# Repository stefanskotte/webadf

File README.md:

# WebFloppy

An Amiga disk library that puts a disk in a real Amiga's floppy drive over WiFi. (The repository keeps the
project's first name, `webadf`.)

Two halves that work together:

- **A web app** for keeping Amiga disk images. Add them, have them identified
  against TOSEC, OpenRetro and Demozoo, organise them into collections, browse and
  edit the files inside a disk, rewind a disk to any earlier version, and send files to
  and from the Amiga.
- **A drive replacement.** An RP2350 board plugs into the Amiga's floppy connector,
  behaves like a DD or HD floppy drive, and plays whichever disk you pick in the web app.
  When the Amiga saves, the changes go back to the library.

Run the web app two ways: use our hosted copy at <https://webadf.vercel.app> (on Vercel), or
host your own with Docker on any amd64 or arm64 machine, a NAS included. A self-hosted copy has every
feature the hosted one has. Firmware updates, the PaulaNET driver disk and the TOSEC catalogue
arrive by themselves; see [docs/self-hosting.md](docs/self-hosting.md).

Pick a disk in the browser, or tap its NFC tag on the drive, and the Amiga reads it.
Workbench 3.1 boots from the board, games load, and saves made on the Amiga show up
in the web app as new versions of the disk.

*Rev B, designed by Shanshe: 34-pin floppy header, floppy power connector, OLED
display, buzzer, a 4-pin header (J4), and a Pimoroni Pico Plus 2 W.
The KiCad project is in `wifi-floppy/hardware/`; check it with `pnpm hw:verify` before
ordering. Rev B has been the bench board since October 2026.*

## Bugs and ideas

Found a bug, or want something WebFloppy does not do yet? Anyone can open an issue at
<https://github.com/stefanskotte/webadf/issues>, for a bug report or a feature request alike. For a bug, say what
you did, what you saw and, for a board, which firmware it runs (Devices shows it).

## Quickstart

Choose where the web app runs. The board's first install is the same either way; only a
self-hosted copy needs one extra step, pointing the board at your server.

### Path A: the hosted web app (Vercel)

You need the board, a USB cable, a phone and an account on <https://webadf.vercel.app>
(registration is by invitation). The board talks to this server out of the box.

1. Hold the **BOOT** button (the Raspberry Pi docs call it BOOTSEL) and plug the board into
   your computer over USB. A drive called `RP2350` appears.
2. Download `wifi-floppy-install-<version>.uf2` from the
   [latest release](https://github.com/stefanskotte/webadf/releases/latest) and drag it onto
   that drive. The board writes it and restarts by itself; the drive disappears.
3. **Get a pairing code in the web app.** The code comes from the web app, not the board. Open
   **Devices**: with no board yet it lists the five steps (**How pairing works** shows them again at any
   time). Press **Pair a device**, give the board a name and press **Get a code**. The code lasts 30 minutes,
   and the page now walks you through the rest with the code filled in.

4. **Give the board your Wi-Fi and the code.** Power the board; its screen shows *Setup needed* and its own
   Wi-Fi network, `wifi-floppy-XXXX`. Join that network from your phone (password `wififloppy`). The
   setup page opens by itself; if it does not, browse to `http://192.168.4.1/`. Enter your home Wi-Fi name
   and password (a 2.4 GHz network with a password) and the code, and press **Save**.

5. **Wait about a minute.** The board's network disappears, the board joins your Wi-Fi and uses the code
   to register with the web app. Keep the Devices page open: it says **Paired** and shows the board by
   itself. If the board cannot join or register, its setup network comes back with the reason at the top
   of the setup page; join it again and fix that. Firmware updates now arrive over the air from the web app.

### Path B: your own server (self-hosted, Docker)

You need a host with Docker and Compose v2, the board, a USB cable and a phone.

1. Install the stack, as [docs/self-hosting.md](docs/self-hosting.md#2-install) describes: download
   `compose.yaml` and `.env.example` (as `.env`) from the newest `web-X.Y.Z` tag, set `WEBADF_URL`
   (for example `https://192.168.1.10`) and `WEBADF_ADMIN_EMAIL` in `.env`, then run
   `docker compose up -d`. Create the account with the link from `docker compose logs app | grep 'first admin'`.
2. Install the firmware as in steps 1-2 of Path A.
3. **Override the server.** The firmware points at the hosted app by default. Open the board's
   USB serial console (any serial terminal, firmware 1.13.0 or newer) and type:

   ```
   wf server set https://192.168.1.10
   wf server tls noverify
   YES
   wf reboot
   ```

   Use your own `WEBADF_URL`. `tls noverify` is needed because a board cannot trust the
   certificate Caddy makes for an IP address or a LAN name; with a public `WEBADF_DOMAIN` and a
   Let's Encrypt certificate, leave it out. `wf server show` prints the setting and
   `wf server clear` goes back to the hosted app. Changing the server forgets the board's
   Wi-Fi and pairing, and it refuses while a disk is mounted.
4. Pair it as in steps 3-5 of Path A, from **Devices** on your own server. Firmware updates come
   from your server too: it imports every signed release from GitHub daily.

If your phone has joined this board's setup network before, forget that network first. More
detail, and what to do when a join fails, is in
[wifi-floppy/README.md](wifi-floppy/README.md#first-install) and, for a self-hosted copy,
[docs/self-hosting.md](docs/self-hosting.md#4-boards).

## Screenshots

The pictures come from a demo account holding freely redistributable disks: scene demos and
freeware tools. `PORT=3100 pnpm screenshots` takes them again (see
`e2e/screenshots.shots.ts`); every email address on them is masked, and the board is a
stand-in called A500. The one exception is Transfer's window, captured from a real A500 by hand.

*The library. Titles are identified against TOSEC and Demozoo; the 9 Fingers card is
outlined and carries a DF0 pill because its disk is in a drive.*

*The drive menu in the header: from any page, see what each board is playing, switch write
protection, step to the next disk or eject.*

*A title page: facts and screenshots from Demozoo, then each disk with its actions.*

*Files: two panes in the Directory Opus style over STASH:, NET: and LIBRARY: (collections are folders there). The pane
you last clicked is the source; the buttons under the panes act on it. Each edit to a disk is a new version in its History.*

*NET: also lists the Amiga's own volumes when Transfer runs there with Read ticked: open a drawer on the hard disk
and copy files to STASH: or LIBRARY:. With Write ticked too, copy and move onto it, rename and delete.*

*Transfer, on the Amiga itself: files from the web app arrive here, and Send goes the other way. Read and Write decide
what the web app may do with the Amiga's volumes.*

*A board on the Devices page. The drawing's screen shows what the board's OLED shows.*

*The display editor: choose the panel, then which elements the OLED draws and where.*

*Adding disks: drop them anywhere on the Library page, or use Add disks (Browse files, Paste a URL). The tray says
what each one did.*

*Help explains the parts that are not obvious.*

*Settings has three tabs: Account (yours alone), Library (sharing) and Server.*

*Sharing, on the Library tab: let a friend's WebFloppy browse and mount your collections. Each link works once.*

*About this server, on the Server tab.*

*On a phone or a tablet (below 1024 px wide), the pages move to a tab bar at the bottom; More holds the rest.*

*The server admin's Overview, for whoever runs the copy.*

## Features

### Library

- Add `.adf`, `.adz`, `.dms`, `.dmz` and `.hfe` by dropping them anywhere on the Library page (folders and
  `.zip` / `.lha` of them too) or through Add disks: Browse files, or Paste a URL to one (or to a `.zip` or `.lha`
  of them, up to 20 MB). Drop `.lha`, `.lzh` and `.zip` archives onto a disk to pick files out of them.
- HD (1.76 MB) ADFs are recognised and tagged HD, and are disks like any other: browsed
  and edited in the browser, with full history.
- Each unique disk is stored once, however many times it is added.
- Disks are identified against TOSEC, OpenRetro and Demozoo, and grouped into titles
  with cover art, screenshots, publisher, year and type.
- A grid of cards or a condensed table, a page at a time; collections (folders in the table),
  disk sets for multi-disk games, and search from the header.
- Create a blank formatted disk: 880 KB or 1.76 MB, OFS or FFS.
- Download any disk as an ADF.
- Works on a phone: below 1024 px the pages move to a tab bar at the bottom.

### Files

- The Files page: two panes over three places. LIBRARY: holds your titles and their disks; STASH: keeps loose
  files for 30 days (what you drop there, and what your Amiga sends); NET: holds what waits to go to each board's
  Amiga, and the Amiga's own volumes. Copy and move between the panes, or drag.
- Browse the AmigaDOS filesystem in the browser: files, folders, free space.
- Add, rename, move and delete files and folders; drop a folder from your computer
  onto a disk; drag entries between folders.
- Every change is a new version. The history panel shows what changed in each
  version, lets you browse any old version, and restores one as a new version.
- HFE images (including long-track formats such as Turrican's) play read-only and can
  be extracted to an ADF when every sector decodes.

### The drive

- Set up from a phone: the board opens a WiFi setup page, you enter your network and
  a pairing code from the web app, and it joins your library.
- Mount and eject from the web app, from the drive menu in the header, or by
  tapping an NFC tag. Next disk steps a multi-disk game on, and the board loads that disk
  ahead of time.
- Reads and writes on a real Amiga. Saves reach the library as new disk versions,
  including saves made while the board was offline.
- Works as DF0, beside a real DF1. Or the board is DF1 as well: holding the next disk of the
  set, or any disk you mount there.
- Plays HD disks: the board tells the Amiga it is an HD drive while an HD disk is in.
  Needs Kickstart 3.0 or later. Playing needs firmware 1.4.1 or later (the web app
  refuses to mount an HD disk on older firmware and says so); saving to an HD disk
  needs 1.5.0 (1.4.x keeps HD write-protected on the board whatever the web app
  says).
- Write protection can be switched from the web app while the disk is in the drive.
- OLED status display (128x32 or 128x64, SSD1306 or SH1106): WiFi strength, what it is
  doing, the disk's name and the current track. A display editor in the web app picks what
  it shows and where. An activity LED blinks on reads.
- Updates its own firmware from the web app. Releases are signed, a failed update
  falls back to the previous firmware, and the board never updates while a disk is
  in the drive.

### Amiga networking

- The board can put the Amiga on your network as DF1, with Rob Smith's PaulaNET driver
  (used with his permission) and a TCP/IP stack such as AmiTCP_NG or Roadshow. The driver disk
  comes from the board itself.
- Send files from your computer, or from a disk in your library, to a folder on the Amiga: on the Files page,
  drop them on Send files to the Amiga, or copy them into a board under NET:. Files the Amiga sends back land in STASH:.
- Transfer, the Amiga program on the driver disk, saves what arrives and sends files up. It runs from Workbench,
  from a Shell, or hidden from WBStartup as a commodity (Ctrl-Alt-W shows it).
- With Transfer's Read ticked, the Files page browses the Amiga's own volumes; with Write ticked too, it copies and
  moves onto them, makes drawers, renames and deletes. Both are off until the Amiga's owner ticks them.
- Setting it up, Transfer, the limits and what to do when something fails:
  [docs/amiga-networking.md](docs/amiga-networking.md).

### NFC tags

- Tap a tag on the drive to mount its disk. Tapping another tag swaps disks; tapping
  the one already in the drive does nothing. A Next-disk card steps to the next disk.
- Write any disk to a tag from the ⋯ menu on its library card, or the NFC button on a
  disk, then tap a tag on the drive; the result appears in the browser.
- A tag only ever mounts disks from your own library.
- Reader: HW-147C (Si512), on the board's I2C bus next to the OLED. PN532 modules work
  from firmware 1.18.0 and are still being tested.

## How it works

An Amiga floppy drive does not deliver blocks. It hands Paula a raw magnetic flux
stream and the Amiga decodes MFM in software, so a drive emulator has to produce flux
at the right rate, continuously, while the disk spins.

```
  browser  ──mount──▶  web app  ──encodes ADF → MFM──▶  device  ──flux──▶  Amiga
     ▲                    │                                │
     └──── new version ◀──┴── Postgres + blobs     RP2350 + 8 MB PSRAM ◀── NFC tag
```

The server encodes a 901,120-byte ADF into 2,027,536 bytes of Amiga MFM and the board
streams it: PIO emits 2 µs bitcells, DMA restarts each revolution and raises INDEX,
giving 300 rpm. The whole disk lives in PSRAM, so a seek is answered immediately
instead of over the network. The board streams flux rather than ADFs, which lets
flux formats such as HFE use the same path.

An HD disk is the exception. The server sends the board the ADF itself (a small
WFAD header, then 1,802,240 bytes), and the board encodes each track to MFM as the
head reaches it, in about 4 ms, well inside the head's settle time. A PIO program
answers the Amiga's drive-ID read on RDY with the HD ID while an HD disk is mounted.
When the Amiga saves to an HD disk, the board checks all 22 sectors of the written
track, keeps them as ADF bytes, and uploads those bytes as they are.

When the Amiga writes, the board decodes the written tracks, uploads them, and the
server records them as a new version of the disk. Versions are stored as sector
deltas.

## Status

| | |
|---|---|
| Web app: library, collections, identification, search | live |
| Add `.adf` `.adz` `.dms` `.hfe` to the library; `.lha`/`.lzh`/`.zip` onto a disk | live |
| File editing inside a disk, blank disks, drag and drop | live |
| Disk history: browse and restore any version | live, restore verified on hardware |
| Device: setup portal, WiFi, TLS, pairing | verified on hardware |
| Mount and eject from the browser and the header's drive menu | verified on hardware |
| Reading on a real Amiga (Workbench 3.1, games) | verified on hardware |
| Writing on a real Amiga, saves reach the library | verified on hardware |
| Second drive (DF1) alongside the board | verified on hardware |
| HFE, including long-track (Turrican) | verified on hardware; weak-bit titles not yet tested |
| HD disks, read-only (Kickstart 3.0+) | verified on hardware (firmware 1.4.1, Kickstart 3.1) |
| HD disks: Amiga saves, history, browser editing, blank HD disks | shipped in firmware 1.5.1; bench steps 4-7 owed (HANDOFF 3ao) |
| Firmware updates from the web app | verified on hardware (current release: 1.21.1) |
| Self-hosting with Docker (compose stack, GHCR image, amd64 + arm64) | live (web-1.1.0); verified with a board and an A500 on an openmediavault NAS |
| NFC: tap to mount, write tags from the web | verified on hardware |
| Amiga networking (PaulaNET as DF1), files to and from the Amiga | verified on hardware (A500) |
| Rev B board | built and running (Shanshe's design, `wifi-floppy/hardware/`) |

## Repository

| Path | What |
|---|---|
| `src/` | the Next.js app |
| `src/lib/adfmfm/` | ADF ⇄ Amiga MFM encoder, verified against Greaseweazle |
| `src/lib/adffs/` | AmigaDOS filesystem reader/writer (OFS/FFS) |
| `src/lib/archive/` | `.lha`/`.lzh`, `.zip` and `.dms` decoders, all browser-side |
| `src/lib/hfe/` | HFE parsing, conversion for the board, ADF extraction |
| `src/lib/disk-history/` | sector deltas and the version chain behind history and restore |
| `src/lib/nfc/` | NFC tap and tag-writing rules and storage |
| `wifi-floppy/firmware/` | the RP2350 firmware (pico-sdk ≥ 2.3.0) |
| `wifi-floppy/hardware/` | the board (KiCad) |
| `docs/superpowers/specs/` | design specs, one per feature |
| `HANDOFF.md` | the engineering log: decisions, measurements, bench results |

## Running it

```bash
pnpm install
pnpm db:dev start         # a local Postgres 18 in Docker; prints its DATABASE_URL
pnpm db:migrate           # apply drizzle/ to DATABASE_URL (there is no db:push)
pnpm dev                  # needs .env.local: DATABASE_URL, BETTER_AUTH_SECRET,
                          # BETTER_AUTH_URL (BLOB_READ_WRITE_TOKEN is optional)
pnpm test                 # vitest, pure logic
pnpm e2e                  # playwright, against the database in .env.local
bash scripts/e2e-local.sh # playwright with no Vercel or Neon: a fresh Postgres in
                          # its own container (webadf-pg-e2e, :55433 -- never the
                          # db:dev one) and local storage; arguments go to playwright
```

Stored files (disk images, covers, firmware) go to local disk under `./data/blobs`
(`STORAGE_DIR` moves it) unless `BLOB_READ_WRITE_TOKEN` is set, in which case they go to
Vercel Blob. On Vercel the token is required: the app refuses to fall back to local disk there.

To run your own copy, use the Docker stack in [docs/self-hosting.md](docs/self-hosting.md)
(Quickstart, [Path B](#path-b-your-own-server-self-hosted-docker)); the commands above are for development.

A self-hosted copy needs no extra setting: Settings → About this server (`/about` leads there) reads
**Self-hosted** unless `SELFHOSTED=false`, which only our own deployment sets. A Docker build
without `.git` can pass `GIT_SHA` so About this server shows the commit.

Firmware:

```bash
export PICO_SDK_PATH=/path/to/pico-sdk        # tag 2.3.0 or later
pnpm firmware:build
pnpm firmware:test                            # host tests, no board needed
pnpm firmware:publish --dry-run               # sign and register a release
```

Write a disk to an NFC tag from the command line:

```bash
pnpm nfc:write "Turrican II disk 1"           # then tap a tag on the drive
```

The setup access point uses the password **`wififloppy`** by default. Set
`PORTAL_AP_PASSWORD` at build time to change it. The pairing code from the web app is
what authorises a board to join a library.

Putting the firmware on a new board is the [Quickstart](#quickstart) above: one
`wifi-floppy-install-<version>.uf2` from the GitHub release, dragged onto the drive that
appears while BOOT is held at power-up. With picotool, `pnpm firmware:install-partitioned` still works.

Every push that touches the firmware is built by
[`.github/workflows/firmware.yml`](.github/workflows/firmware.yml), which runs the host
tests and publishes a `.uf2` with a `manifest.json` (version, commit, size, SHA-256).

## Verification

Each layer that talks to hardware or to an undocumented format is checked against an
independent implementation:

| | checked against |
|---|---|
| `pnpm adfmfm:diff` | Greaseweazle's `amigados` codec |
| `pnpm adffs:verify` | `xdftool` |
| `pnpm lha:verify` | the real `lha` binary |
| `pnpm dms:verify` | xDMS, the implementation ours was ported from |

## Licence

- **Software** (the web app, scripts and the wifi-floppy firmware source): [MIT](LICENSE).
- **Hardware** (`wifi-floppy/hardware/`, the board design): [CERN-OHL-P-2.0](wifi-floppy/hardware/LICENSE), the
  permissive open-hardware licence, so anyone can build, modify and sell their own boards. The rev B PCB layout is
  Shanshe's work, licensed this way with Shanshe's agreement; see
  [wifi-floppy/hardware/NOTICE.md](wifi-floppy/hardware/NOTICE.md).
- **Third-party code, the libraries in the firmware image, and acknowledgements**: see
  [THIRD-PARTY-NOTICES.md](THIRD-PARTY-NOTICES.md). The Wi-Fi driver bundled with the Pico SDK is licensed for use
  on Raspberry Pi chips (which this board is).

This project builds on Nano-Tek, OpenFlops, Keir Fraser's FlashFloppy and Greaseweazle, and the other work credited
in the notices file.

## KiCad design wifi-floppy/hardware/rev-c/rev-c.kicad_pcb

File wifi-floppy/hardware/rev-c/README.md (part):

# Rev C: on-board RP2350, schematic and routed board

Rev B with the PIM726 module replaced by its parts on our PCB: RP2350B, 16 MB flash, 16 MB PSRAM, RM2 radio, crystal, core regulator, USB-C, BOOTSEL, SWD. Every GPIO stays where the PIM726 has it, so the firmware's pin map and the pico-sdk board definition are unchanged. Same outline as rev B, widened 13.1 mm to the left on 2026-11-17 for a second floppy connector (J5 EXT DRV, an original drive as DF0) and made 2 mm taller at the top on 2026-11-18 for larger connector labels: see "Original drive connector". Rev B's files are untouched.

**The schematic and the routed board agree, and nothing else about the board differs from using a PIM726 on rev B. It is still not a board to order:** see "Owed before a fab order".

## Result (2026-11-05, copper revised 2026-11-11 and 2026-11-16, original-drive connector added 2026-11-17)

| Check | Result |
|---|---|
| Layers | 4: signals on F.Cu and B.Cu, GND on In1, +3.3 V on In2 |
| KiCad DRC, with schematic parity | 0 unconnected, 0 errors, 0 parity differences. 38 warnings: the 25 from before (21 M1's outline over its own pads, 3 silkscreen at the board edge, one 0.03 mm neck somewhere in the top ground pour, not located) and 13 new: 11 where the SOT-23 and MSOP outlines of U6, U7, U8 and Q9 reach the new left edge, and 2 where the side label SEL2 touches J5's and J9's outlines (the strip is 3.6 mm wide) |
| ERC | 0 errors, 0 warnings |
| `verify_sch.py` | all 82 multi-pin nets match, whatever they are called |
| `verify_pins.py rev-c.kicad_pcb` | 212 of 212 against the RP2350 datasheet, firmware `board.c`, the pico-sdk header, the RM2 datasheet, and rev B's connected pads (U2 pin 2 is checked as the mux's output, SEL0M_B, and the mux's SEL0 input as rev B's U2 pin 2 net; J2 pin 1 as +5V_IN into F1, and F1's output as rev B's J2 pin 1 net) |
| `verify_reg.py` | the regulator matches Raspberry Pi's pattern: 62 differences before, 0 now |
| `pnpm hw:verify rev-c` | passes: ERC, DRC, firmware pins, J1 lines, 1k pull-ups, the regulator, and the original-drive checks (J5's pins against J1's, the sense pins, the pull-ups, U6/Q9/U7/U8/J8/J9 pins), and the power protection (J2/J8 pin 1 into F1/F2, both fuses out to +5V, D5 across +5V and GND) |
| `check45.py rev-c.kicad_pcb` | passes: every track at a multiple of 45 degrees, every bend 45 or 90 degrees, no short leg between two bends. It lets through, and lists on every run, the regulator's own tracks (10 flags) and two 0.1 mm steps at U1 pins 71 and 73; see "Routing rule" |
| Gerbers | regenerated 2026-11-18 for the keyed power headers and their fuses, same 14 files and export settings; 313 holes for 210 vias and 103 drilled pads. Not analysed with kicad-happy, not through JLC's own check |
| Tracks | 0.15 mm, necked to 0.11 mm at the QFN, vias 0.45/0.2 mm, spacing 0.127 mm: within JLC's published 4-layer limits, not confirmed by JLC |

## Copper review, 2026-11-11

A read of the autorouted copper found nine things to fix. Shanshe's hand re-route had not arrived, so they were fixed on this board with scripted and hand-placed tracks. Seven were fixed with the parts where they stood; the operator then allowed placement changes for the last two, QSPI and the USB pair. Each change was kept only if DRC (with parity), `verify_reg.py`, `verify_pins.py` and `hw:verify rev-c` still passed. The regulator's pattern is untouched.

| | Before | Now |
|---|---|---|
| 1. IOVDD pins tracked to their 100 nF capacitor on the top layer | 1 of 11 (pin 64) | 7 of 11: 5, 29, 41, 50, 60, 76 added, 1.5 to 2.4 mm each; their vias under the chip are gone, so the capacitor's via is the pin's way to the plane |
| 2. C15 to DVDD pin 32 | 15.4 mm, 2 vias | 2.2 mm on the top layer |
| 3. QSPI, U1 to PSRAM (CLK, SD0, SD1, SD2, SD3) | 14.5, 27.7, 33.7, 14.3, 15.1 mm | 8.3, 8.1, 15.0, 13.8, 8.2 mm |
| 3. QSPI, U1 to flash | 13.1, 13.5, 19.4, 18.4, 15.5 mm | 12.9, 10.0, 19.1, 16.5, 15.4 mm |
| 3. QSPI, vias on those five lines | 9 | 5: none on CLK, SD0 and SD3, three on SD1, two on SD2 |
| 3. QSPI, longest branch past a junction | 16.0 mm (SD0, through the flash to the PSRAM) | 13.5 mm (SD1 to the flash); CLK, SD0 and SD3 have no branch |
| 3. Chip selects | QCS 23.0 mm, 3 vias; PSRAM_CS 20.5 mm, none | QCS **unchanged**; PSRAM_CS 21.5 mm, none |
| 4. USB D+/D-, gap between the two, median | 3.8 mm, one each side of L1 | 0.15 mm, together on the back |
| 4. USB D+/D-, resistor to pin | 15.7 and 17.5 mm, 2 vias each | 16.6 and 17.1 mm, 2 vias each |
| 5. Crystal: XIN, pin to Y1 | 9.7 mm, 2 vias, through C25's pad | 7.2 mm, no vias, between Y1's ground pads |
| 5. WL_D beside the crystal | between R22's pads, 0.65 mm from Y1 | crosses under XIN and XOUT on the back at the pins; 0.7 mm from R22 and 1.8 mm from Y1; 4 vias instead of 2 |
| 5. WL_ON below Y1 | 0.5 mm from the XIN pad | 1.0 mm |
| 5. Ground plane under Y1 | 98% | 100% |
| 6. VBUS, J6 A4/B9 to D3 | 0.2 mm wide, 9.3 mm, 0.5/0.25 vias | 0.5 mm wide, 6.9 mm, 0.7/0.35 vias; VBUS is in the Reg class (`rules.py`) |
| 7. Plane vias inside an SMD pad | 28 | 9 |
| 8. Segments under 0.05 mm | 82 (58 of zero length) | 0 |
| 8. Joints under 45 degrees | 6 | 0 |
| 9. CC1 between R26 and R28 | 0.09 mm for 0.3 mm | 0.15 mm |
| Whole board | 972 segments, 180 vias | 855 segments, 168 vias |

What was not done, and why:

- **QSPI (3), placement changed.** U4 is turned half a turn and moved 0.9 mm west; R24 moved onto the PSRAM_CS run by R20, and C28 to below U4's supply pin. U3 and C20 stay. With U4 this way round, SD0, CLK and SD3 run on the top layer from U1 into U4's pads and out of them to U3's: no vias and no branch, over unbroken ground. SD1 and SD2 are on U4's far row and U3's far column, and U1's pin order puts them on the wrong side of the other three, so each branches at a via below U4 and hops under them on the back. What is not better: SD1 is still 19 mm to the flash, now through two vias; the flash lengths are spread wider (6.3 mm before, 9.1 now) because the short lines got shorter, none longer; PSRAM_CS is 1.0 mm longer; QCS was not touched, because C20 stands over its pin and it can only leave U1 inwards.
- **USB pair (4), placement not changed.** Both lines leave pins 67 and 66 to the north-west on the top layer (the only way pin 66 can go), drop through a via each beside the regulator's keep-out, run the back 0.15 mm apart above the regulator, and come up at a via each beside R25 and R26. R25 and R26 were not swapped: at J6 the D+ pads come out west of D-, and CC2 and CC1 pass west, south and east of the two resistors, so a top-layer pair has no way out of that pocket whichever resistor stands where; with the vias the present order needs no crossing. Two vias a line is the least this layout allows. A pair with no vias would need R28 moved to J6's west side (or vias on CC2) and vias on PSRAM_CS instead; not done. The pair is on the back, so its reference is the +3.3 V plane, not ground; both planes are whole under it but for the vias' own holes. It is 12 Mbit/s.
- **IOVDD pins 15 and 24** keep their vias under the chip: TRK0 on the top layer lies between pin 15 and C12, and WL_ON's via sits below pin 24 with WPROT on the back leaving it nowhere else to go. **Pins 68 and 69** have no capacitor this side of the USB pins.
- **C23 to DVDD pins 51 and 10** (9.6 and 13.0 mm, two vias) is Raspberry Pi's back track and the ring under the chip: the pattern, so it stays.
- **Via-in-pad, 9 left:** RM2's six ground castellations (the only free copper beside them is under the module), U5's two tab vias (the regulator's output and heat go through them) and U2 pin 19 (no free spot within 2 mm).
- **VSYS and VBUS still cross under Y1 on the back**, behind both planes.
- The link between J6's two VBUS pin pairs is still 0.2 mm: the connector's locating holes leave no room for more.

XIN now runs under the crystal's body, between its two ground pads. That is short and has ground on both sides, but it is under the can: say if you would rather have it go round.

## Routing rule, 2026-11-16

The operator's rule (2026-11-15): every track runs at a multiple of 45 degrees, and each bend turns by exactly 45 or 90 degrees: no sharp corners, and no turn built from several small kinks. `check45.py` is the rule as a check; it read 203 flags on the 2026-11-11 board. The copper was fixed where it lay, not routed again, so the copper review's fixes above are kept. Each change was kept only if nothing came closer than its clearance, and the whole board was then put through DRC (with parity), `verify_reg.py`, `verify_pins.py` and `hw:verify rev-c`.

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
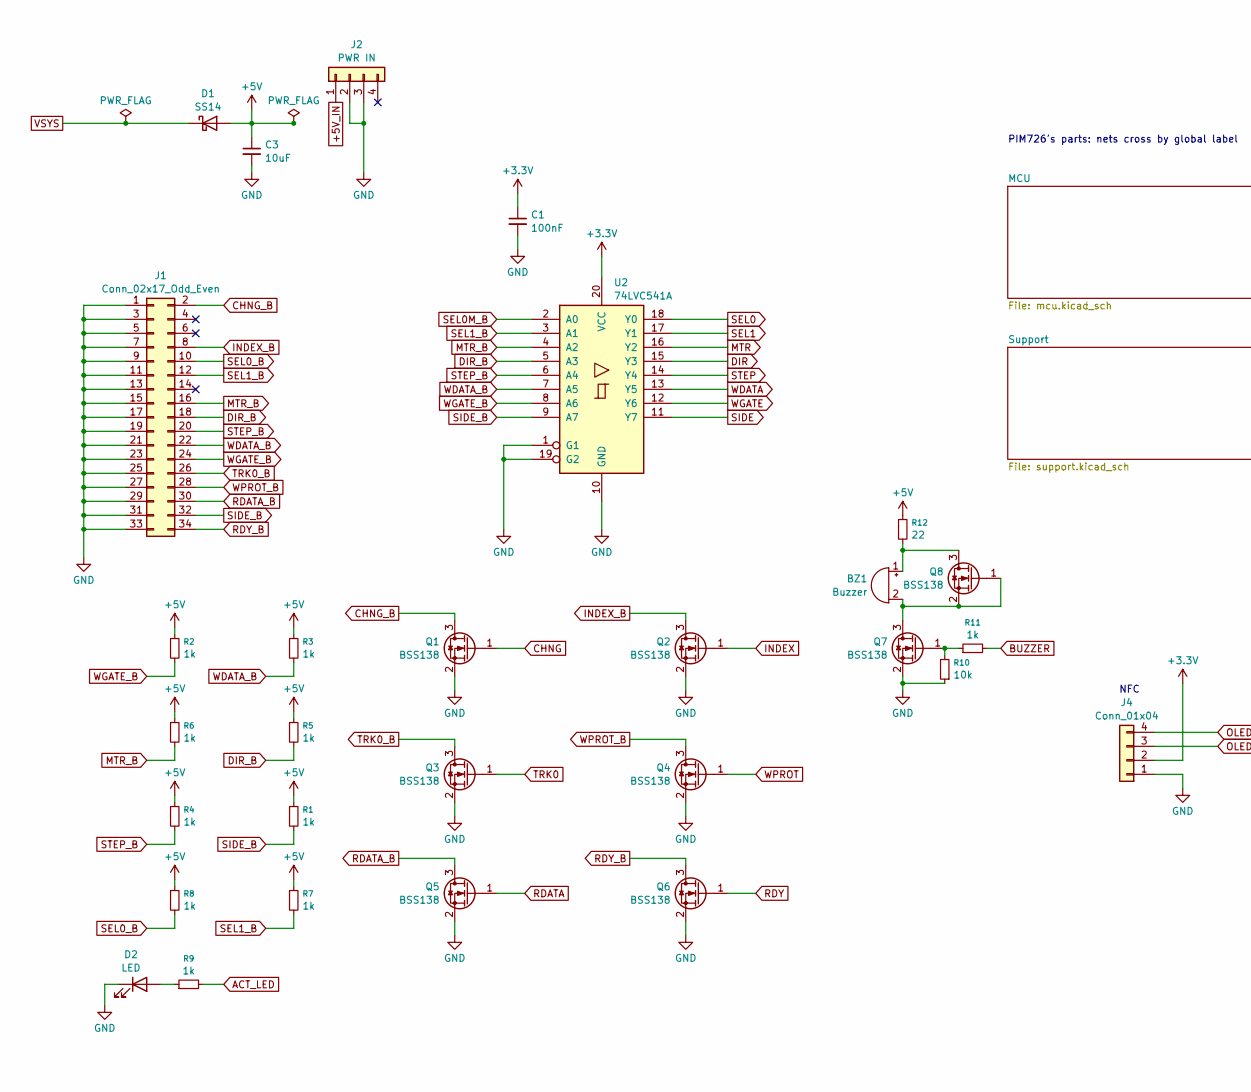
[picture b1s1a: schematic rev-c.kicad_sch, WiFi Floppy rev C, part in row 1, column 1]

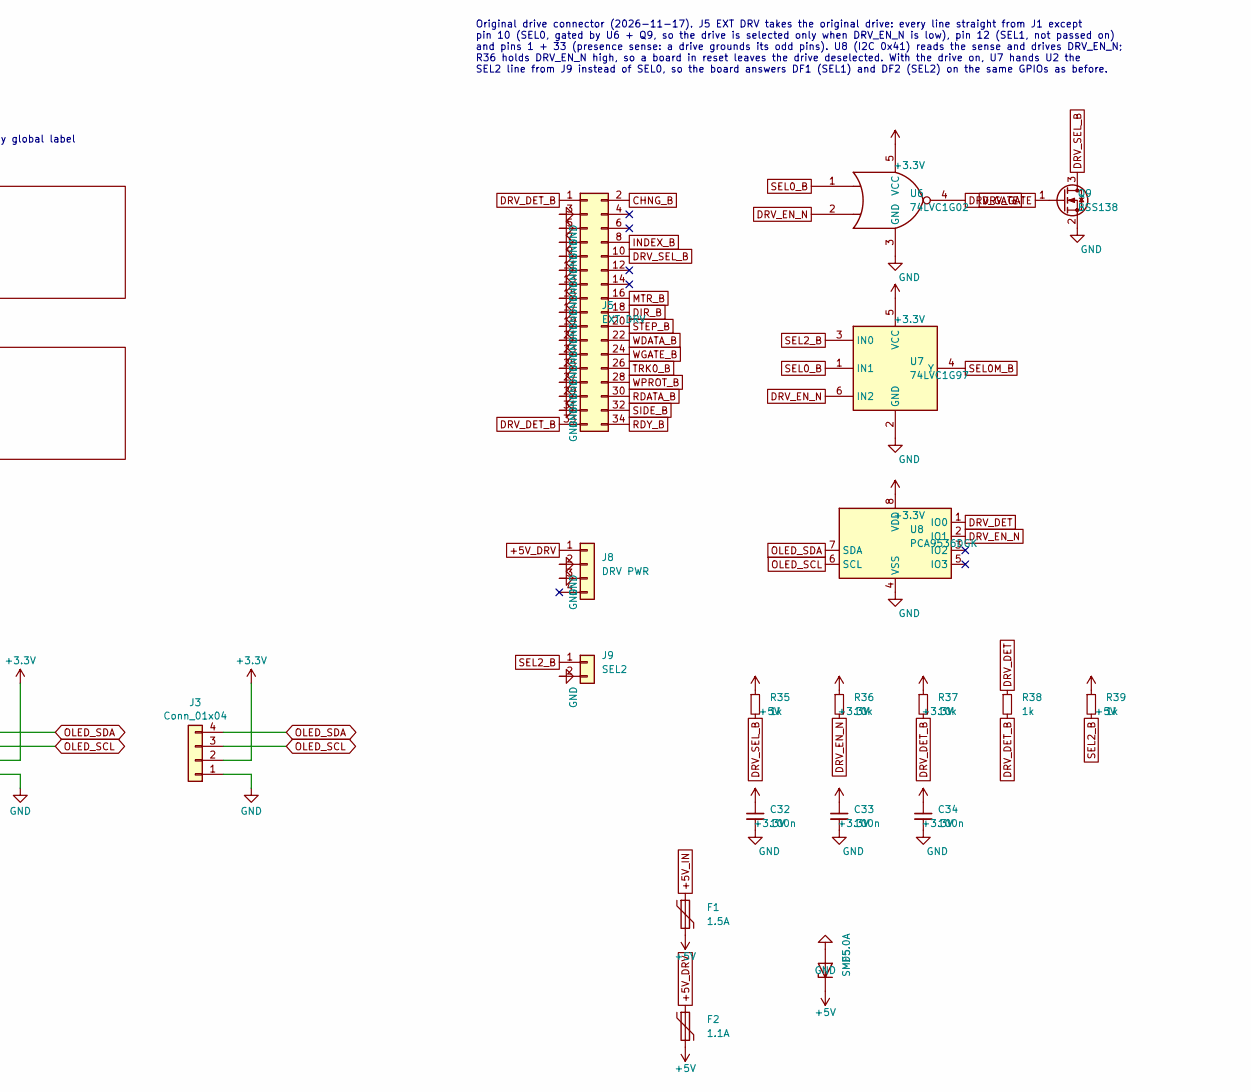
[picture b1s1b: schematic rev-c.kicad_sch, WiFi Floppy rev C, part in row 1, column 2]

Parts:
BZ1: Buzzer; PinHeader_1x02_P2.54mm_Vertical
C1: 100nF; C_1206_3216Metric_Pad1.33x1.80mm_HandSolder
C3: 10uF; C_1206_3216Metric_Pad1.33x1.80mm_HandSolder
C32, C33, C34: 100n; C_0402_1005Metric
D1: SS14; D_SMA_Handsoldering
D2: LED; LED_1206_3216Metric_Pad1.42x1.75mm_HandSolder; LCSC C49018
D5: SMF5.0A; D_SOD-123F; LCSC C2758488
F1: 1.5A; Fuse_1206_3216Metric; LCSC C22379952
F2: 1.1A; Fuse_1206_3216Metric; LCSC C46970781
J1: Conn_02x17_Odd_Even; IDC-Header_2x17_P2.54mm_Vertical
J2: PWR IN; TE_AMP_EI_171825-4_1x04_P2.50mm_Vertical
J3, J4: Conn_01x04; PinHeader_1x04_P2.54mm_Vertical
J5: EXT DRV; IDC-Header_2x17_P2.54mm_Vertical
J8: DRV PWR; TE_AMP_EI_171825-4_1x04_P2.50mm_Vertical
J9: SEL2; PinHeader_1x02_P2.54mm_Vertical
Q1, Q2, Q3, Q4, Q5, Q6, Q7, Q8, Q9: BSS138; SOT-23
R1, R2, R3, R4, R5, R6, R7, R8, R9, R11: 1k; R_1206_3216Metric_Pad1.30x1.75mm_HandSolder; LCSC C1469
R10: 10k; R_1206_3216Metric_Pad1.30x1.75mm_HandSolder; LCSC C1489
R12: 22; R_1206_3216Metric_Pad1.30x1.75mm_HandSolder; LCSC C2925020
R35, R38, R39: 1k; R_0402_1005Metric
R36, R37: 10k; R_0402_1005Metric
U2: 74LVC541A; SOIC-20W_7.5x15.4mm_P1.27mm; LCSC DNP
U6: 74LVC1G02; SOT-23-5
U7: 74LVC1G97; SOT-23-6
U8: PCA9536DGK; MSOP-8_3x3mm_P0.65mm

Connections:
+3.3V: C1.1, C32.1, C33.1, C34.1, J3.2, J4.2, R36.1, R37.1, U2.20 (VCC), U6.5 (VCC), U7.5 (VCC), U8.8 (VDD); also elsewhere on the board
+5V: C3.1, D1.2 (A), D5.1 (K), F1.2, F2.2, R1.1, R2.1, R3.1, R4.1, R5.1, R6.1, R7.1, R8.1, R12.1, R35.1, R39.1
+5V_DRV: F2.1, J8.1
+5V_IN: F1.1, J2.1
ACT_LED: R9.2; also elsewhere on the board
BUZZER: R11.2; also elsewhere on the board
CHNG: Q1.1 (G); also elsewhere on the board
CHNG_B: J1.2, J5.2, Q1.3 (D)
DIR: U2.15 (Y3); also elsewhere on the board
DIR_B: J1.18, J5.18, R5.2, U2.5 (A3)
DRV_DET: R38.1, U8.1 (IO0)
DRV_DET_B: J5.1, J5.33, R37.2, R38.2
DRV_EN_N: R36.2, U6.2, U7.6 (IN2), U8.2 (IO1)
DRV_GATE: Q9.1 (G), U6.4
DRV_SEL_B: J5.10, Q9.3 (D), R35.2
GND: C1.2, C3.2, C32.2, C33.2, C34.2, D2.1 (K), D5.2 (A), J1.1, J1.3, J1.5, J1.7, J1.9, J1.11, J1.13, J1.15, J1.17, J1.19, J1.21, J1.23, J1.25, J1.27, J1.29, J1.31, J1.33, J2.2, J2.3, J3.1, J4.1, J5.3, J5.5, J5.7, J5.9, J5.11, J5.13, J5.15, J5.17, J5.19, J5.21, J5.23, J5.25, J5.27, J5.29, J5.31, J8.2, J8.3, J9.2, Q1.2 (S), Q2.2 (S), Q3.2 (S), Q4.2 (S), Q5.2 (S), Q6.2 (S), Q7.2 (S), Q9.2 (S), R10.1, U2.1 (G1), U2.10 (GND), U2.19 (G2), U6.3 (GND), U7.2 (GND), U8.4 (VSS); also elsewhere on the board
INDEX: Q2.1 (G); also elsewhere on the board
INDEX_B: J1.8, J5.8, Q2.3 (D)
MTR: U2.16 (Y2); also elsewhere on the board
MTR_B: J1.16, J5.16, R6.2, U2.4 (A2)
unnamed: BZ1.1 (+), Q8.3 (D), R12.2
unnamed: BZ1.2 (-), Q7.3 (D), Q8.1 (G), Q8.2 (S)
unnamed: D2.2 (A), R9.1
unnamed: Q7.1 (G), R10.2, R11.1
OLED_SCL: J3.3, J4.3, U8.6 (SCL); also elsewhere on the board
OLED_SDA: J3.4, J4.4, U8.7 (SDA); also elsewhere on the board
RDATA: Q5.1 (G); also elsewhere on the board
RDATA_B: J1.30, J5.30, Q5.3 (D)
RDY: Q6.1 (G); also elsewhere on the board
RDY_B: J1.34, J5.34, Q6.3 (D)
SEL0: U2.18 (Y0); also elsewhere on the board
SEL0M_B: U2.2 (A0), U7.4 (Y)
SEL0_B: J1.10, R8.2, U6.1, U7.1 (IN1)
SEL1: U2.17 (Y1); also elsewhere on the board
SEL1_B: J1.12, R7.2, U2.3 (A1)
SEL2_B: J9.1, R39.2, U7.3 (IN0)
SIDE: U2.11 (Y7); also elsewhere on the board
SIDE_B: J1.32, J5.32, R1.2, U2.9 (A7)
STEP: U2.14 (Y4); also elsewhere on the board
STEP_B: J1.20, J5.20, R4.2, U2.6 (A4)
TRK0: Q3.1 (G); also elsewhere on the board
TRK0_B: J1.26, J5.26, Q3.3 (D)
VSYS: D1.1 (K); also elsewhere on the board
WDATA: U2.13 (Y5); also elsewhere on the board
WDATA_B: J1.22, J5.22, R3.2, U2.7 (A5)
WGATE: U2.12 (Y6); also elsewhere on the board
WGATE_B: J1.24, J5.24, R2.2, U2.8 (A6)
WPROT: Q4.1 (G); also elsewhere on the board
WPROT_B: J1.28, J5.28, Q4.3 (D)

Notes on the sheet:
PIM726's parts: nets cross by global label
NFC
Original drive connector (2026-11-17). J5 EXT DRV takes the original drive: every line straight from J1 except pin 10 (SEL0, gated by U6 + Q9, so the drive is selected only when DRV_EN_N is low), pin 12 (SEL1, not passed on) and pins 1 + 33 (presence sense: a drive grounds its odd pins). U8 (I2C 0x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

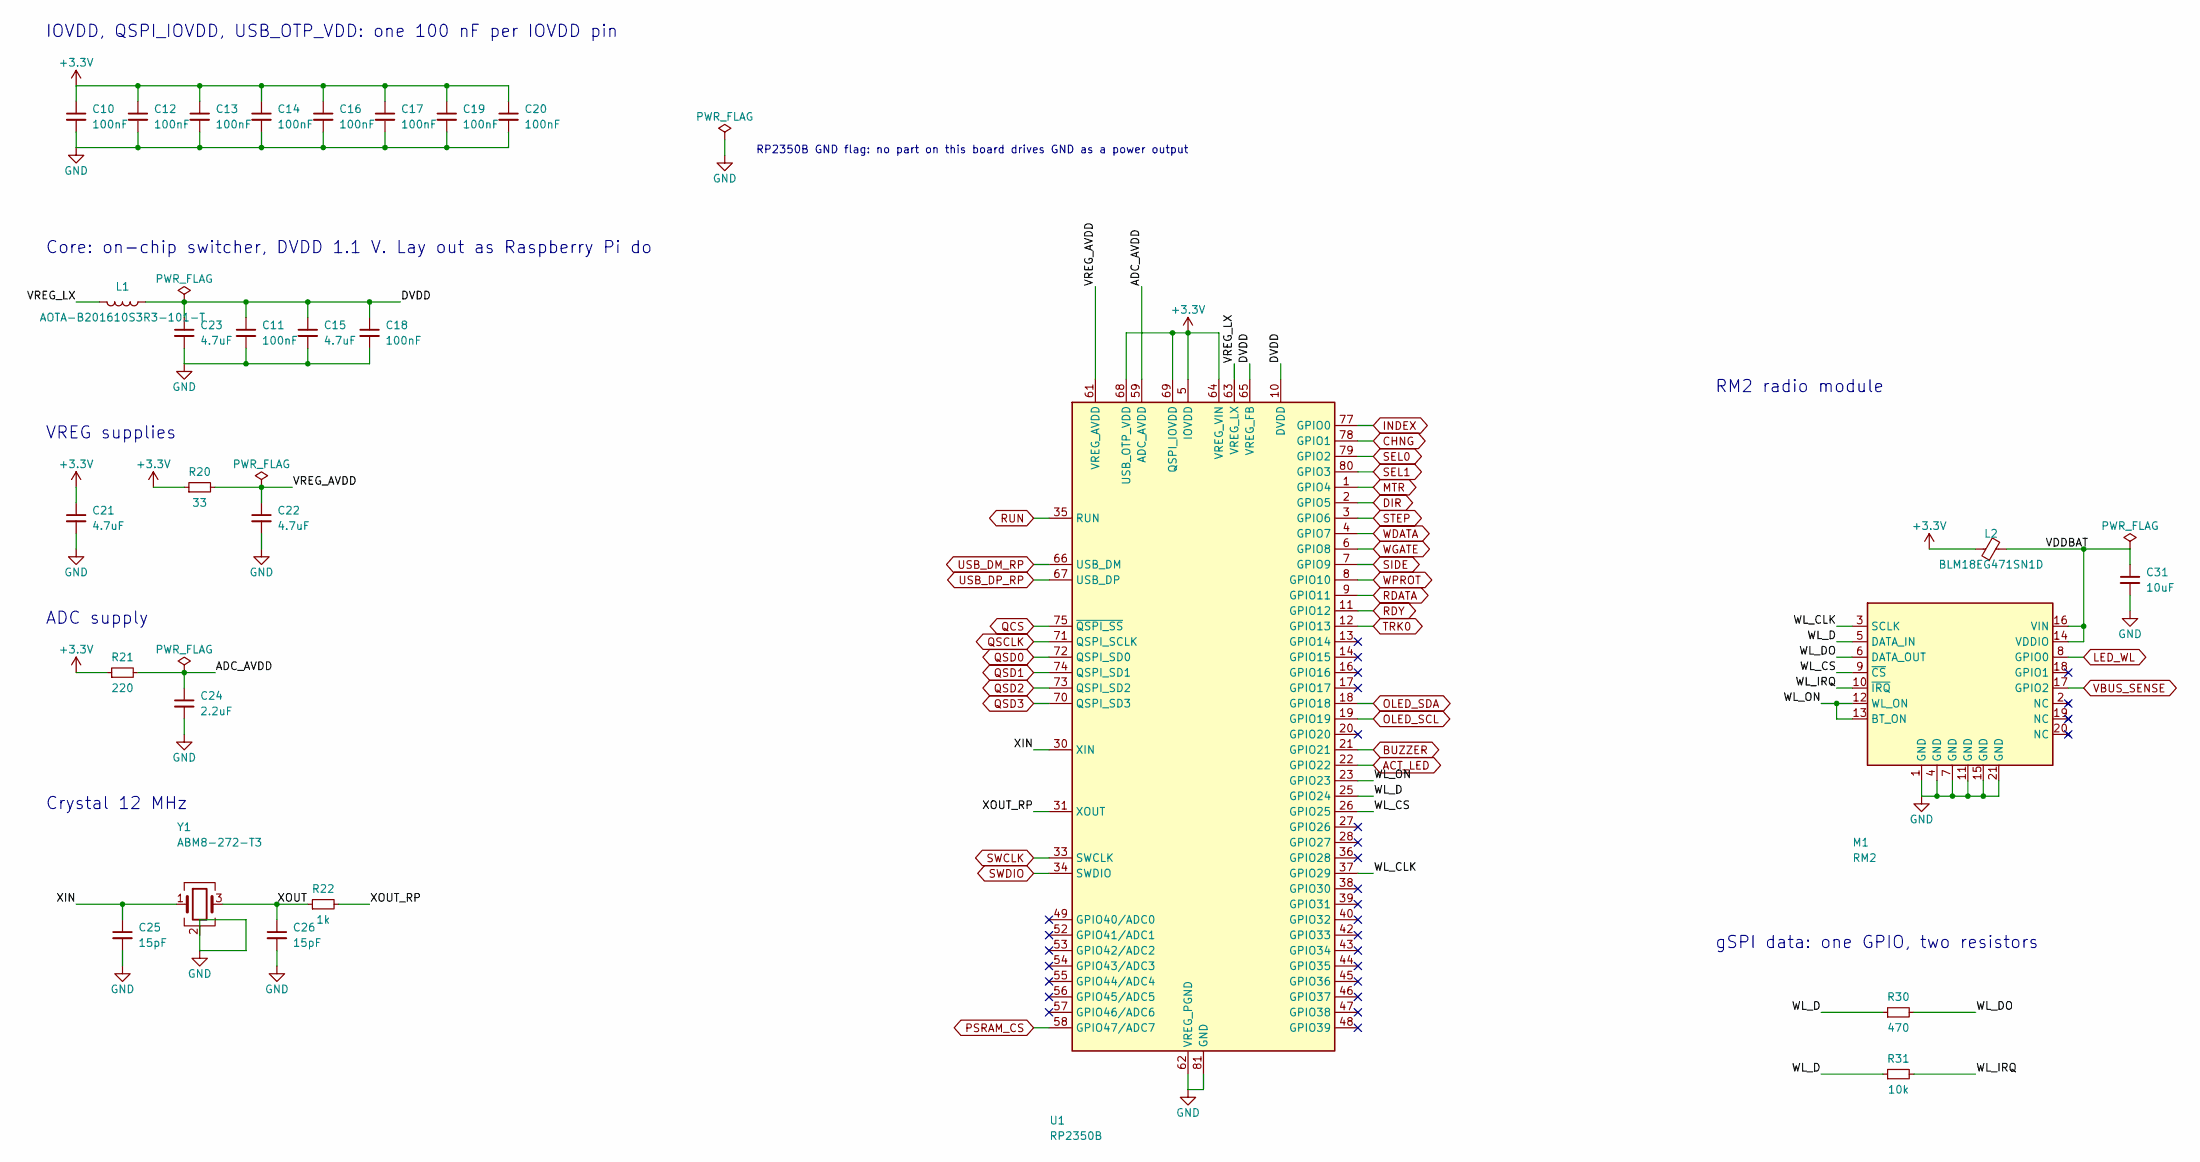
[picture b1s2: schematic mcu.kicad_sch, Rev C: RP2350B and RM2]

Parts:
C10, C11, C12, C13, C14, C16, C17, C18, C19, C20: 100nF; C_0402_1005Metric
C15, C22: 4.7uF; C_0402_1005Metric
C21, C23: 4.7uF; C_0402_1005Metric_RP_wide
C24: 2.2uF; C_0603_1608Metric
C25, C26: 15pF; C_0402_1005Metric
C31: 10uF; C_0603_1608Metric
L1: AOTA-B201610S3R3-101-T; L_Abracon_AOTA-B201610S3R3-101-T; MPN AOTA-B201610S3R3-101-T
L2: BLM18EG471SN1D; L_0603_1608Metric; MPN BLM18EG471SN1D
M1: RM2; Raspberry_Pi_RM2; MPN Raspberry Pi RM2
R20: 33; R_0402_1005Metric
R21: 220; R_0402_1005Metric
R22: 1k; R_0402_1005Metric
R30: 470; R_0402_1005Metric
R31: 10k; R_0402_1005Metric
U1: RP2350B; QFN-80-1EP_10x10mm_P0.4mm_EP3.4x3.4mm_ThermalVias; MPN RP2350B
Y1: ABM8-272-T3; Crystal_SMD_3225-4Pin_3.2x2.5mm

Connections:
+3.3V: C10.1, C12.1, C13.1, C14.1, C16.1, C17.1, C19.1, C20.1, C21.1, L2.1, R20.1, R21.1, U1.5 (IOVDD), U1.15 (IOVDD), U1.24 (IOVDD), U1.29 (IOVDD), U1.41 (IOVDD), U1.50 (IOVDD), U1.60 (IOVDD), U1.64 (VREG_VIN), U1.68 (USB_OTP_VDD), U1.69 (QSPI_IOVDD), U1.76 (IOVDD); also elsewhere on the board
/MCU/ADC_AVDD: C24.1, R21.2, U1.59 (ADC_AVDD)
/MCU/DVDD: C11.1, C15.1, C18.1, C23.1, L1.1, U1.10 (DVDD), U1.32 (DVDD), U1.51 (DVDD), U1.65 (VREG_FB)
/MCU/VDDBAT: C31.1, L2.2, M1.14 (VDDIO), M1.16 (VIN)
/MCU/VREG_AVDD: C22.1, R20.2, U1.61 (VREG_AVDD)
/MCU/VREG_LX: L1.2, U1.63 (VREG_LX)
/MCU/WL_CLK: M1.3 (SCLK), U1.37 (GPIO29)
/MCU/WL_CS: M1.9 (~CS), U1.26 (GPIO25)
/MCU/WL_D: M1.5 (DATA_IN), R30.1, R31.1, U1.25 (GPIO24)
/MCU/WL_DO: M1.6 (DATA_OUT), R30.2
/MCU/WL_IRQ: M1.10 (~IRQ), R31.2
/MCU/WL_ON: M1.12 (WL_ON), M1.13 (BT_ON), U1.23 (GPIO23)
/MCU/XIN: C25.1, U1.30 (XIN), Y1.1
/MCU/XOUT: C26.1, R22.1, Y1.3
/MCU/XOUT_RP: R22.2, U1.31 (XOUT)
ACT_LED: U1.22 (GPIO22); also elsewhere on the board
BUZZER: U1.21 (GPIO21); also elsewhere on the board
CHNG: U1.78 (GPIO1); also elsewhere on the board
DIR: U1.2 (GPIO5); also elsewhere on the board
GND: C10.2, C11.2, C12.2, C13.2, C14.2, C15.2, C16.2, C17.2, C18.2, C19.2, C20.2, C21.2, C22.2, C23.2, C24.2, C25.2, C26.2, C31.2, M1.1 (GND), M1.4 (GND), M1.7 (GND), M1.11 (GND), M1.15 (GND), M1.21 (GND), U1.62 (VREG_PGND), U1.81 (GND), Y1.2 (G), Y1.4 (G); also elsewhere on the board
INDEX: U1.77 (GPIO0); also elsewhere on the board
LED_WL: M1.8 (GPIO0); also elsewhere on the board
MTR: U1.1 (GPIO4); also elsewhere on the board
OLED_SCL: U1.19 (GPIO19); also elsewhere on the board
OLED_SDA: U1.18 (GPIO18); also elsewhere on the board
PSRAM_CS: U1.58 (GPIO47/ADC7); also elsewhere on the board
QCS: U1.75 (~QSPI_SS); also elsewhere on the board
QSCLK: U1.71 (QSPI_SCLK); also elsewhere on the board
QSD0: U1.72 (QSPI_SD0); also elsewhere on the board
QSD1: U1.74 (QSPI_SD1); also elsewhere on the board
QSD2: U1.73 (QSPI_SD2); also elsewhere on the board
QSD3: U1.70 (QSPI_SD3); also elsewhere on the board
RDATA: U1.9 (GPIO11); also elsewhere on the board
RDY: U1.11 (GPIO12); also elsewhere on the board
RUN: U1.35 (RUN); also elsewhere on the board
SEL0: U1.79 (GPIO2); also elsewhere on the board
SEL1: U1.80 (GPIO3); also elsewhere on the board
SIDE: U1.7 (GPIO9); also elsewhere on the board
STEP: U1.3 (GPIO6); also elsewhere on the board
SWCLK: U1.33 (SWCLK); also elsewhere on the board
SWDIO: U1.34 (SWDIO); also elsewhere on the board
TRK0: U1.12 (GPIO13); also elsewhere on the board
USB_DM_RP: U1.66 (USB_DM); also elsewhere on the board
USB_DP_RP: U1.67 (USB_DP); also elsewhere on the board
VBUS_SENSE: M1.17 (GPIO2); also elsewhere on the board
WDATA: U1.4 (GPIO7); also elsewhere on the board
WGATE: U1.6 (GPIO8); also elsewhere on the board
WPROT: U1.8 (GPIO10); also elsewhere on the board

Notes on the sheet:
Crystal 12 MHz
RP2350B GND flag: no part on this board drives GND as a power output
ADC supply
gSPI data: one GPIO, two resistors
VREG supplies
RM2 radio module
IOVDD, QSPI_IOVDD, USB_OTP_VDD: one 100 nF per IOVDD pin
Core: on-chip switcher, DVDD 1.1 V. Lay out as Raspberry Pi do

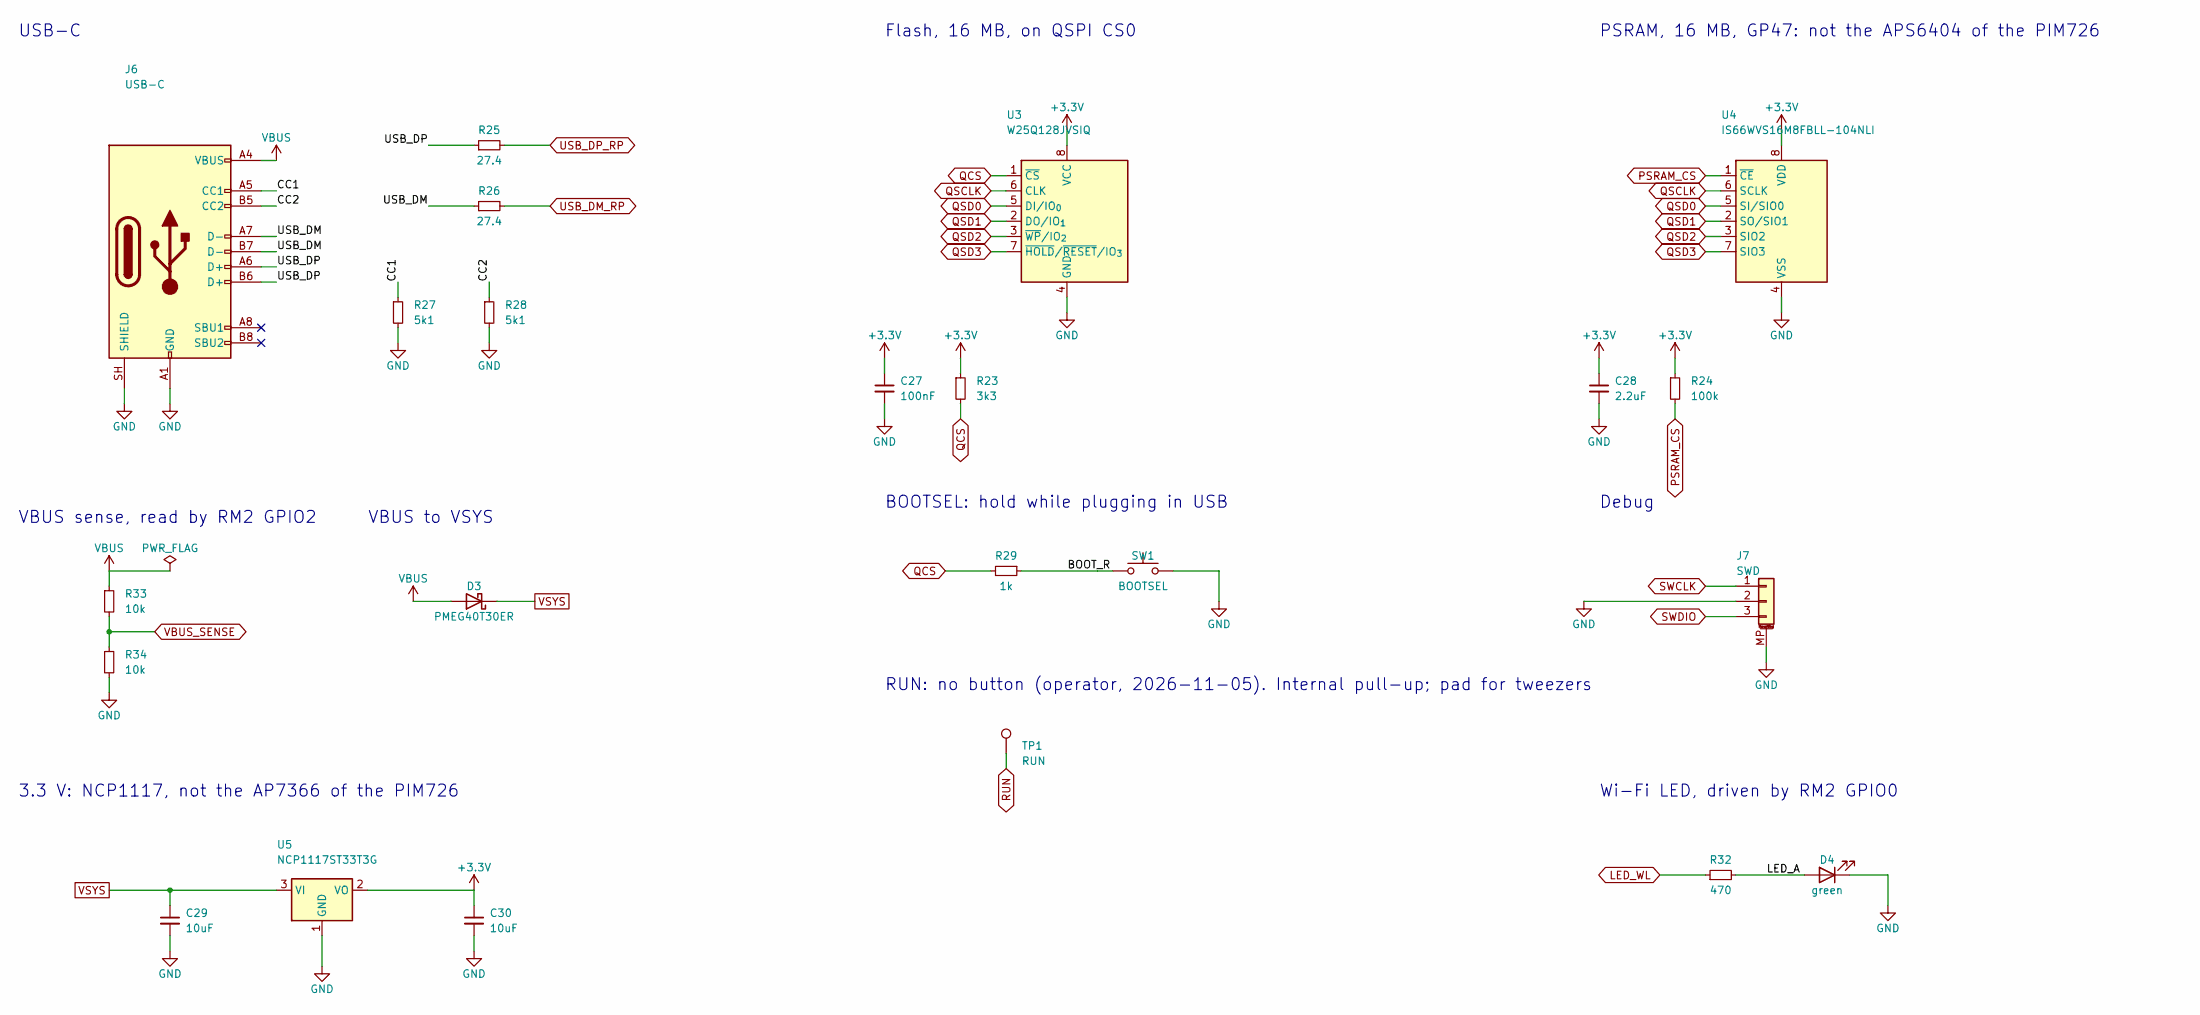
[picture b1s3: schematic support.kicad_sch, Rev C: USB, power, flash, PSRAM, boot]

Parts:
C27: 100nF; C_0402_1005Metric
C28: 2.2uF; C_0603_1608Metric
C29, C30: 10uF; C_0603_1608Metric
D3: PMEG40T30ER; D_SOD-123F; MPN PMEG40T30ER
D4: green; LED_0603_1608Metric
J6: USB-C; USB_C_Receptacle_HRO_TYPE-C-31-M-12; MPN HRO TYPE-C-31-M-12
J7: SWD; JST_SH_BM03B-SRSS-TB_1x03-1MP_P1.00mm_Vertical; MPN JST BM03B-SRSS-TB
R23: 3k3; R_0402_1005Metric
R24: 100k; R_0402_1005Metric
R25, R26: 27.4; R_0402_1005Metric
R27, R28: 5k1; R_0402_1005Metric
R29: 1k; R_0402_1005Metric
R32: 470; R_0402_1005Metric
R33, R34: 10k; R_0402_1005Metric
SW1: BOOTSEL; SW_Push_1P1T_XKB_TS-1187A; MPN XKB TS-1187A
TP1: RUN; TestPoint_Pad_D1.0mm
U3: W25Q128JVSIQ; SOIC-8_5.3x5.3mm_P1.27mm; MPN W25Q128JVSIQ
U4: IS66WVS16M8FBLL-104NLI; SOIC-8_3.9x4.9mm_P1.27mm; MPN IS66WVS16M8FBLL-104NLI
U5: NCP1117ST33T3G; SOT-223-3_TabPin2; MPN NCP1117ST33T3G

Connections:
+3.3V: C27.1, C28.1, C30.1, R23.1, R24.1, U3.8 (VCC), U4.8 (VDD), U5.2 (VO); also elsewhere on the board
/Support/BOOT_R: R29.1, SW1.1
/Support/CC1: J6.A5 (CC1), R27.1
/Support/CC2: J6.B5 (CC2), R28.1
/Support/LED_A: D4.2 (A), R32.2
/Support/USB_DM: J6.A7 (D-), J6.B7 (D-), R26.1
/Support/USB_DP: J6.A6 (D+), J6.B6 (D+), R25.1
GND: C27.2, C28.2, C29.2, C30.2, D4.1 (K), J6.A1 (GND), J6.A12 (GND), J6.B1 (GND), J6.B12 (GND), J6.SH (SHIELD), J7.2, J7.MP (MountPin), R27.2, R28.2, R34.2, SW1.2, U3.4 (GND), U4.4 (VSS), U5.1 (GND); also elsewhere on the board
LED_WL: R32.1; also elsewhere on the board
PSRAM_CS: R24.2, U4.1 (~CE); also elsewhere on the board
QCS: R23.2, R29.2, U3.1 (~CS); also elsewhere on the board
QSCLK: U3.6 (CLK), U4.6 (SCLK); also elsewhere on the board
QSD0: U3.5 (DI/IO_{0}), U4.5 (SI/SIO0); also elsewhere on the board
QSD1: U3.2 (DO/IO_{1}), U4.2 (SO/SIO1); also elsewhere on the board
QSD2: U3.3 (~WP/IO_{2}), U4.3 (SIO2); also elsewhere on the board
QSD3: U3.7 (~HOLD/~RESET/IO_{3}), U4.7 (SIO3); also elsewhere on the board
RUN: TP1.1; also elsewhere on the board
SWCLK: J7.1; also elsewhere on the board
SWDIO: J7.3; also elsewhere on the board
USB_DM_RP: R26.2; also elsewhere on the board
USB_DP_RP: R25.2; also elsewhere on the board
VBUS: D3.2 (A), J6.A4 (VBUS), J6.A9 (VBUS), J6.B4 (VBUS), J6.B9 (VBUS), R33.1
VBUS_SENSE: R33.2, R34.1; also elsewhere on the board
VSYS: C29.1, D3.1 (K), U5.3 (VI); also elsewhere on the board

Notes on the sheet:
VBUS to VSYS
PSRAM, 16 MB, GP47: not the APS6404 of the PIM726
Flash, 16 MB, on QSPI CS0
BOOTSEL: hold while plugging in USB
Debug
USB-C
VBUS sense, read by RM2 GPIO2
3.3 V: NCP1117, not the AP7366 of the PIM726
Wi-Fi LED, driven by RM2 GPIO0
RUN: no button (operator, 2026-11-05). Internal pull-up; pad for tweezers

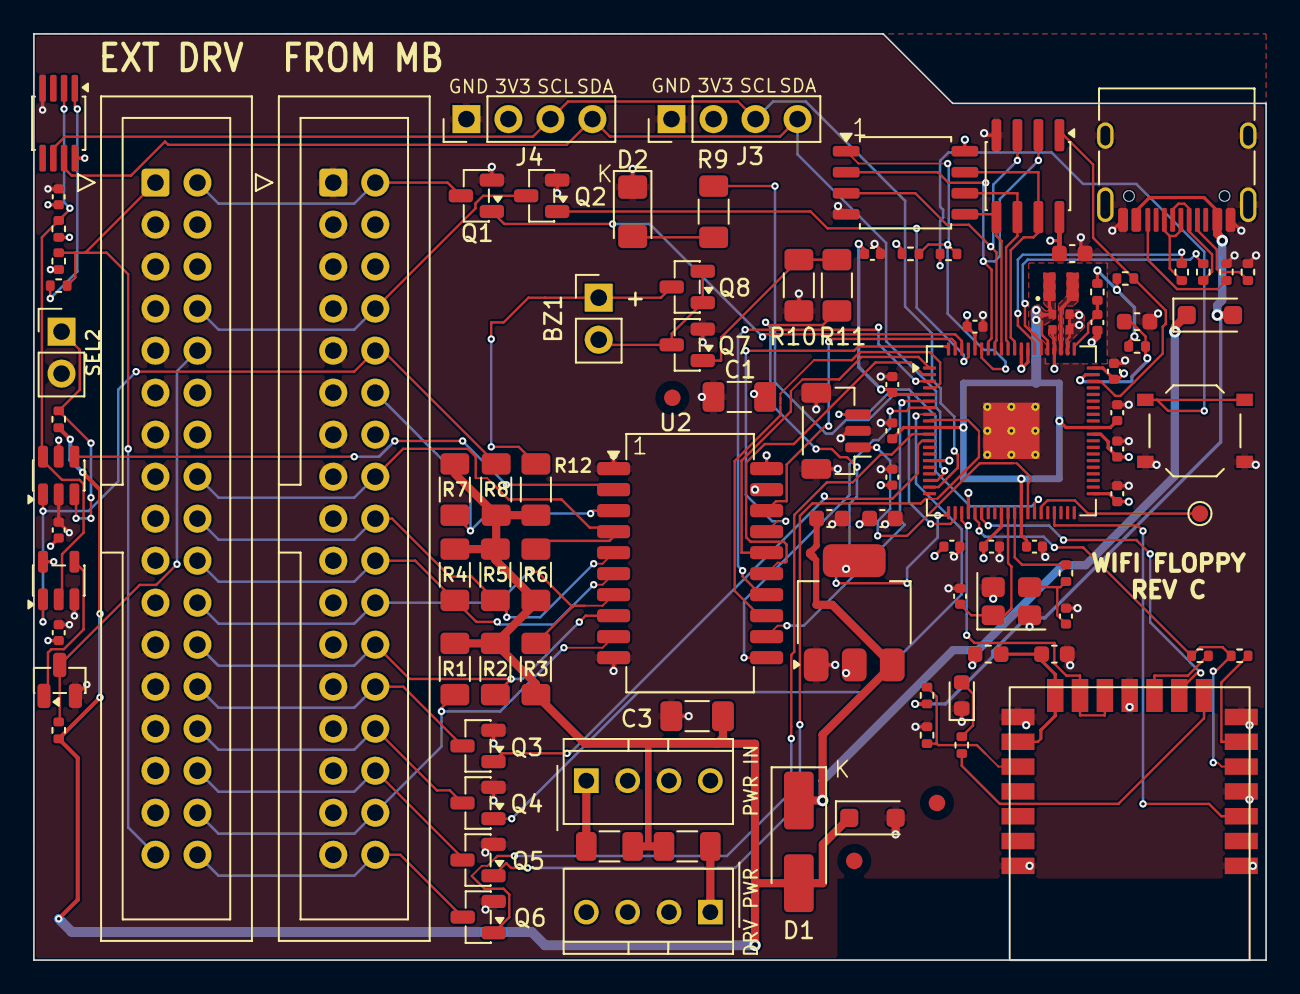
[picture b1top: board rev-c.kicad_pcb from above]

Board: 4 copper layers, 74.5 x 56.0 mm, 102 parts (0 on the bottom side), 84 nets.

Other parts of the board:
FID1, FID2, FID3: Fiducial_1mm_Mask2mm
